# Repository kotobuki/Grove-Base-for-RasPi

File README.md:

# Grove Base for Raspberry Pi

A bridge between the [**Grove**](http://www.seeedstudio.com/wiki/Category:Grove) family by the Seeed Studio and [Raspberry Pi](https://www.raspberrypi.org/) by the Raspberry Pi Foundation.

## Bill of Materials

|Part/Designator|Manufacture Part Number/Seeed SKU|Quantity|
|---------------|---------------------------------|--------|
|PCB||1|
|J1,J2,J3,J4|Seeed SKU: [320110034](http://www.seeedstudio.com/depot/index.php?main_page=opl_info&opl_id=24)|4|
|JP1|Digi-Key: [S9200-ND](http://www.digikey.com/product-search/en?keywords=S9200-ND)|1|

## How to 'compile'?

Place an order at the [Fusion PCBA prototype](http://www.seeedstudio.com/service/index.php?r=pcb) service.

## Compatible Modules

* Sensors
  * [Grove - Button](http://www.seeedstudio.com/wiki/Grove_-_Button) (as a digital input device, can be used as an analog input device)
  * [Grove - Switch(P)](http://www.seeedstudio.com/wiki/Grove_-_Switch(P))
  * [Grove - Touch Sensor](http://www.seeedstudio.com/wiki/Grove_-_Touch_Sensor)
* Actuators
  * [Grove - LED Socket Kit](http://www.seeedstudio.com/wiki/Grove_-_LED)
  * [Grove - Buzzer](http://www.seeedstudio.com/wiki/Grove_-_Buzzer)

# License Information

This design document is licensed by Shigeru Kobayashi under the terms of the [Creative Commons Attribution-ShareAlike 4.0 International Public License](http://creativecommons.org/licenses/by-sa/4.0/).

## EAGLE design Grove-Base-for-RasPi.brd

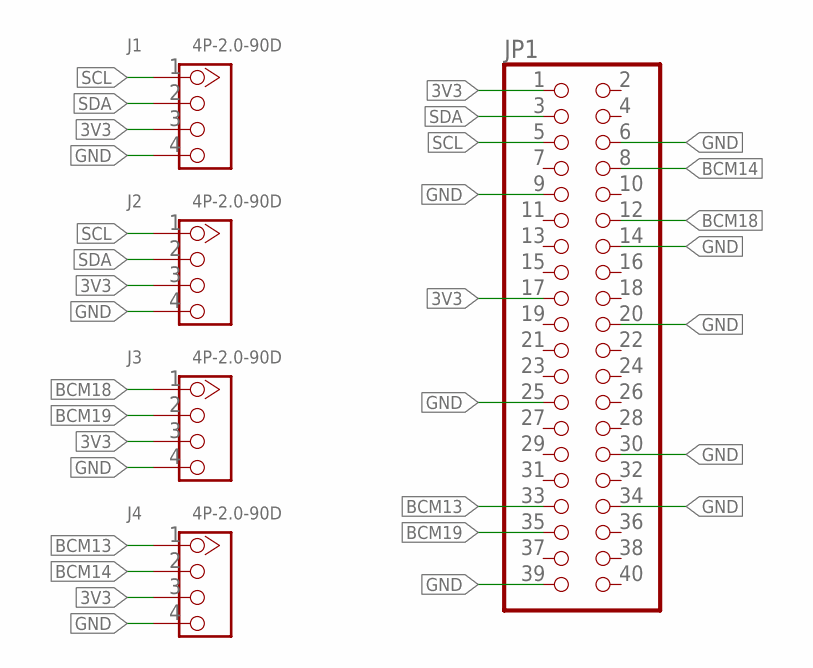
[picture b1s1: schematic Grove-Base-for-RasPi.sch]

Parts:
J1, J2, J3, J4: 4P-2.0-90D; HW4-2.0-90D
JP1: PINHD-2X20; 2X20

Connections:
3V3: J1.3, J2.3, J3.3, J4.3, JP1.1, JP1.17
BCM13: J4.1, JP1.33
BCM14: J4.2, JP1.8
BCM18: J3.1, JP1.12
BCM19: J3.2, JP1.35
GND: J1.4, J2.4, J3.4, J4.4, JP1.6, JP1.9, JP1.14, JP1.20, JP1.25, JP1.30, JP1.34, JP1.39
SCL: J1.1, J2.1, JP1.5
SDA: J1.2, J2.2, JP1.3

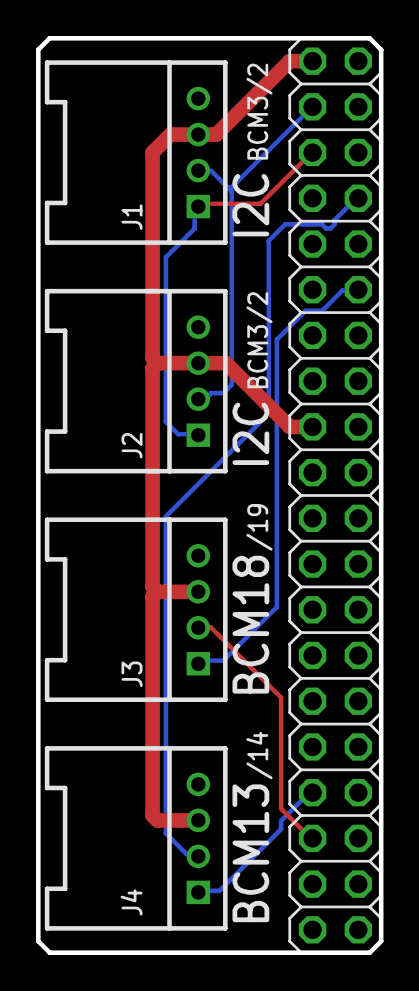
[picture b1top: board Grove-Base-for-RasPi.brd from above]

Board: 2 copper layers, 19.1 x 50.8 mm, 5 parts (0 on the bottom side), 8 nets.

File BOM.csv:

Part/Designator,Manufacture Part Number/Seeed SKU,Quantity"J1,J2,J3,J4",320110034,4JP1,S9200-ND,1

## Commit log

2016-05-22 Add production related files
2016-06-24 Add a picture
